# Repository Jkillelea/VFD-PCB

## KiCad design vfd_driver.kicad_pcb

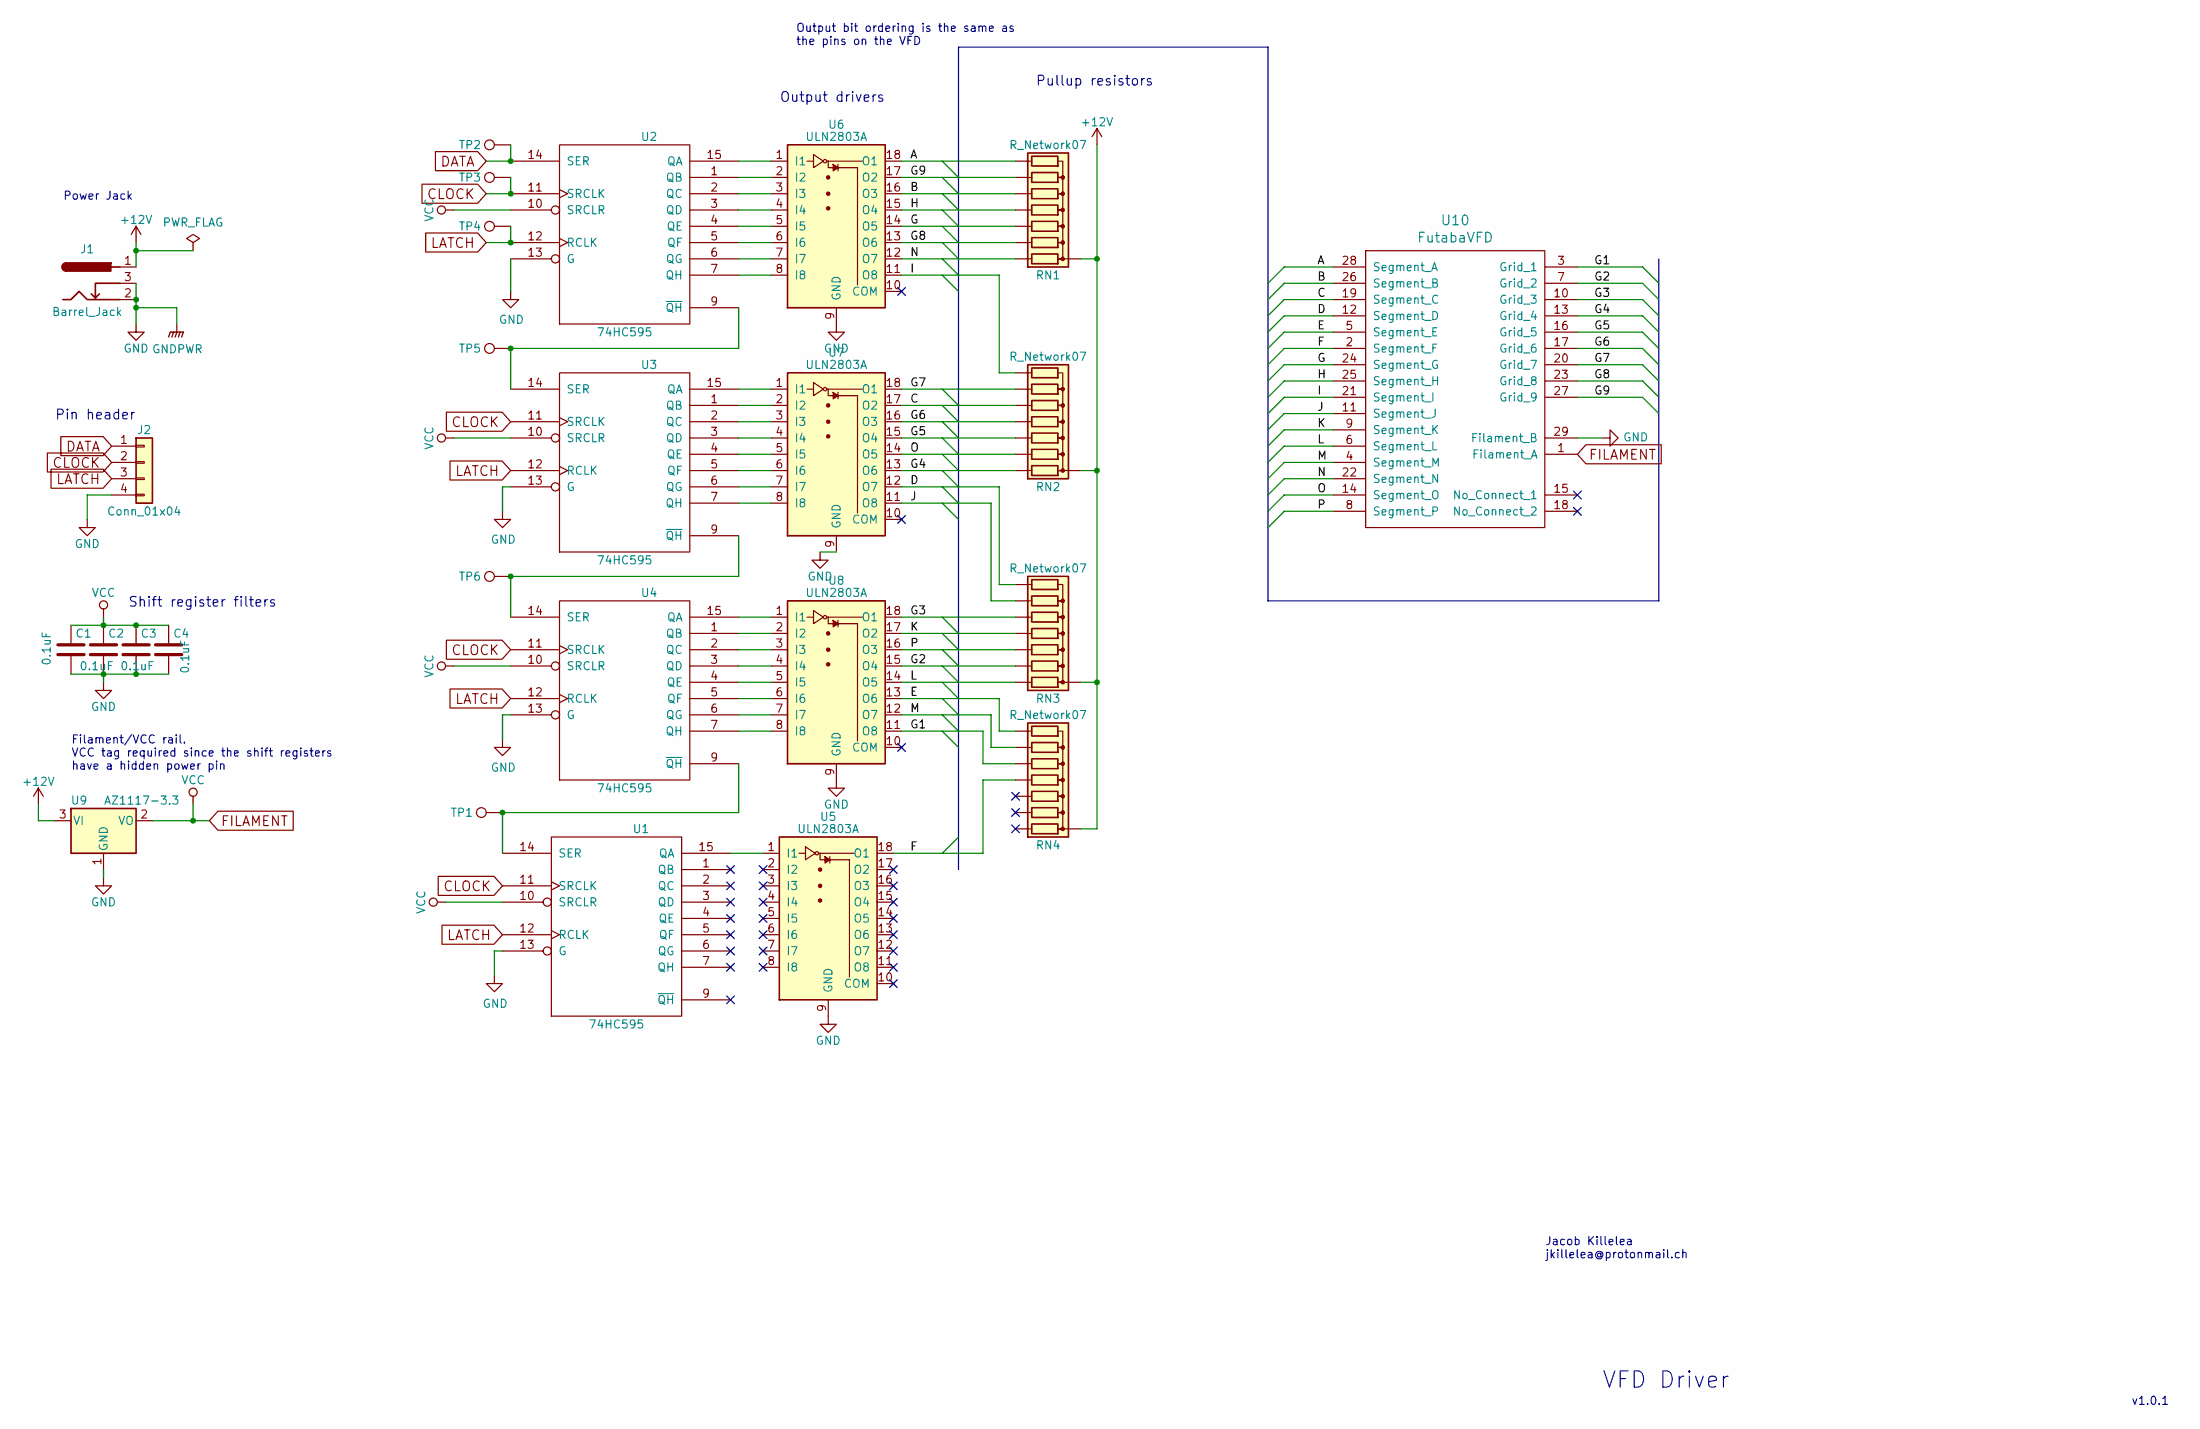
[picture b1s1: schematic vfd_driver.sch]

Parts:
C1, C2, C3, C4: 0.1uF; C_Disc_D4.3mm_W1.9mm_P5.00mm
J1: Barrel_Jack; BARREL_JACK
J2: Conn_01x04; Pin_Header_Angled_1x04_Pitch2.54mm
RN1, RN2, RN3, RN4: R_Network07; R_Array_SIP8
TP1, TP2, TP3, TP4, TP5, TP6: TestPoint; TestPoint_Pad_D1.0mm
U1, U2, U3, U4: 74HC595; DIP-16_W7.62mm_LongPads
U5, U6, U7, U8: ULN2803A; DIP-18_W7.62mm_LongPads
U9: AZ1117-3.3; TO-220-3_Horizontal_Reversed
U10: FutabaVFD; Futaba VFD

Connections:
+12V: J1.1, RN1.1 (common), RN2.1 (common), RN3.1 (common), RN4.1 (common), U9.3 (VI)
/A: RN1.8 (R7), U6.18 (O1), U10.28 (Segment_A)
/B: RN1.6 (R5), U6.16 (O3), U10.26 (Segment_B)
/C: RN2.6 (R5), U7.17 (O2), U10.19 (Segment_C)
/D: RN3.8 (R7), U7.12 (O7), U10.12 (Segment_D)
/E: RN4.8 (R7), U8.13 (O6), U10.5 (Segment_E)
/F: RN4.5 (R4), U5.18 (O1), U10.2 (Segment_F)
/G: RN1.4 (R3), U6.14 (O5), U10.24 (Segment_G)
/G1: RN4.6 (R5), U8.11 (O8), U10.3 (Grid_1)
/G2: RN3.3 (R2), U8.15 (O4), U10.7 (Grid_2)
/G3: RN3.6 (R5), U8.18 (O1), U10.10 (Grid_3)
/G4: RN2.2 (R1), U7.13 (O6), U10.13 (Grid_4)
/G5: RN2.4 (R3), U7.15 (O4), U10.16 (Grid_5)
/G6: RN2.5 (R4), U7.16 (O3), U10.17 (Grid_6)
/G7: RN2.7 (R6), U7.18 (O1), U10.20 (Grid_7)
/G8: RN1.3 (R2), U6.13 (O6), U10.23 (Grid_8)
/G9: RN1.7 (R6), U6.17 (O2), U10.27 (Grid_9)
/H: RN1.5 (R4), U6.15 (O4), U10.25 (Segment_H)
/I: RN2.8 (R7), U6.11 (O8), U10.21 (Segment_I)
/J: RN3.7 (R6), U7.11 (O8), U10.11 (Segment_J)
/K: RN3.5 (R4), U8.17 (O2), U10.9 (Segment_K)
/L: RN3.2 (R1), U8.14 (O5), U10.6 (Segment_L)
/M: RN4.7 (R6), U8.12 (O7), U10.4 (Segment_M)
/N: RN1.2 (R1), U6.12 (O7), U10.22 (Segment_N)
/O: RN2.3 (R2), U7.14 (O5), U10.14 (Segment_O)
/P: RN3.4 (R3), U8.16 (O3), U10.8 (Segment_P)
CLOCK: J2.2, TP3.1, U1.11 (SRCLK), U2.11 (SRCLK), U3.11 (SRCLK), U4.11 (SRCLK)
DATA: J2.1, TP2.1, U2.14 (SER)
FILAMENT: C1.1, C2.1, C3.1, C4.1, U1.10 (SRCLR), U1.16 (VCC), U2.10 (SRCLR), U2.16 (VCC), U3.10 (SRCLR), U3.16 (VCC), U4.10 (SRCLR), U4.16 (VCC), U9.2 (VO), U10.1 (Filament_A)
GND: C1.2, C2.2, C3.2, C4.2, J1.2, J1.3, J2.4, U1.8 (GND), U1.13 (G), U2.8 (GND), U2.13 (G), U3.8 (GND), U3.13 (G), U4.8 (GND), U4.13 (G), U5.9 (GND), U6.9 (GND), U7.9 (GND), U8.9 (GND), U9.1 (GND), U10.29 (Filament_B)
LATCH: J2.3, TP4.1, U1.12 (RCLK), U2.12 (RCLK), U3.12 (RCLK), U4.12 (RCLK)
unnamed: TP1.1, U1.14 (SER), U4.9 (~QH)
unnamed: TP5.1, U2.9 (~QH), U3.14 (SER)
unnamed: TP6.1, U3.9 (~QH), U4.14 (SER)
unnamed: U1.15 (QA), U5.1 (I1)
unnamed: U2.1 (QB), U6.2 (I2)
unnamed: U2.2 (QC), U6.3 (I3)
unnamed: U2.3 (QD), U6.4 (I4)
unnamed: U2.4 (QE), U6.5 (I5)
unnamed: U2.5 (QF), U6.6 (I6)
unnamed: U2.6 (QG), U6.7 (I7)
unnamed: U2.7 (QH), U6.8 (I8)
unnamed: U2.15 (QA), U6.1 (I1)
unnamed: U3.1 (QB), U7.2 (I2)
unnamed: U3.2 (QC), U7.3 (I3)
unnamed: U3.3 (QD), U7.4 (I4)
unnamed: U3.4 (QE), U7.5 (I5)
unnamed: U3.5 (QF), U7.6 (I6)
unnamed: U3.6 (QG), U7.7 (I7)
unnamed: U3.7 (QH), U7.8 (I8)
unnamed: U3.15 (QA), U7.1 (I1)
unnamed: U4.1 (QB), U8.2 (I2)
unnamed: U4.2 (QC), U8.3 (I3)
unnamed: U4.3 (QD), U8.4 (I4)
unnamed: U4.4 (QE), U8.5 (I5)
unnamed: U4.5 (QF), U8.6 (I6)
unnamed: U4.6 (QG), U8.7 (I7)
unnamed: U4.7 (QH), U8.8 (I8)
unnamed: U4.15 (QA), U8.1 (I1)

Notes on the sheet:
Pullup resistors
Output drivers
Shift register filters
Pin header
VFD Driver
v1.0.1
Jacob Killelea jkillelea@protonmail.ch
Power Jack
Filament/VCC rail. VCC tag required since the shift registers have a hidden power pin
Output bit ordering is the same as the pins on the VFD

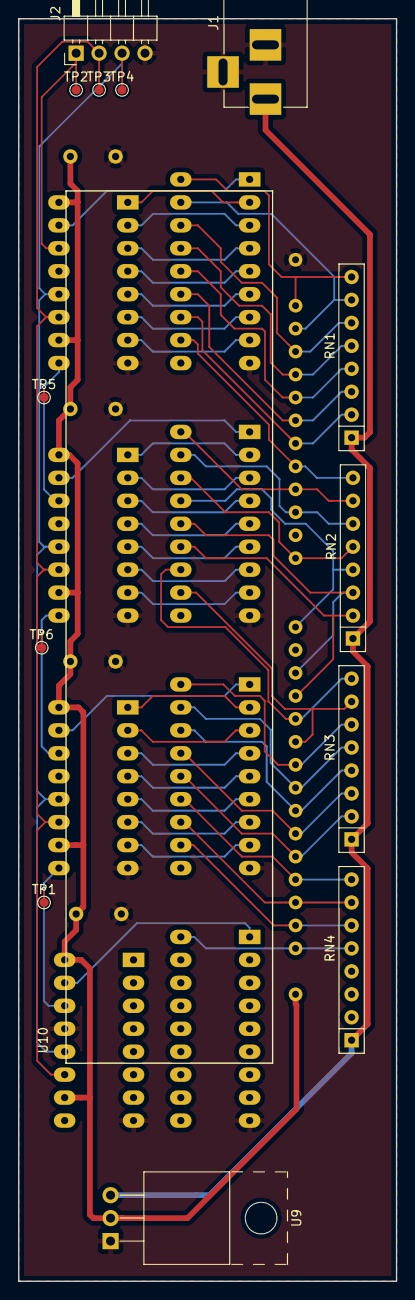
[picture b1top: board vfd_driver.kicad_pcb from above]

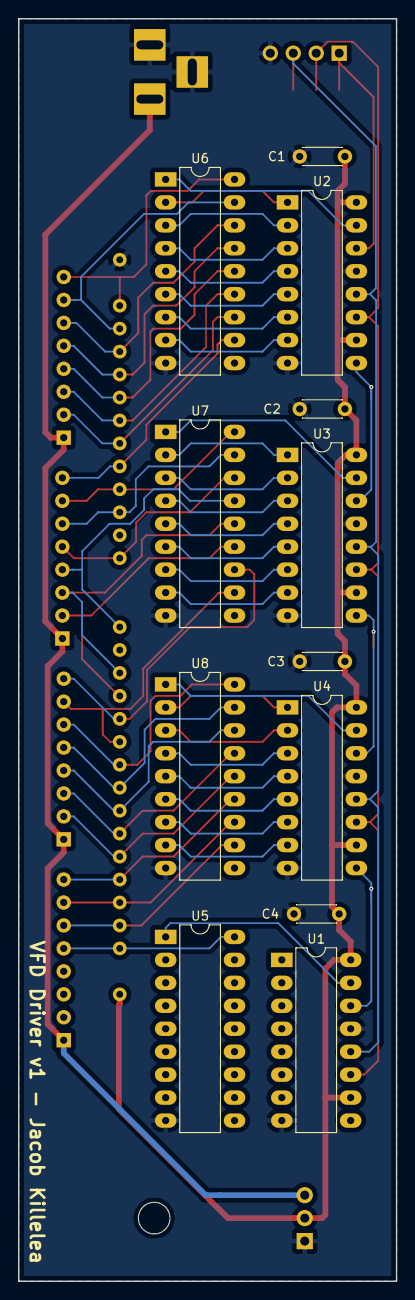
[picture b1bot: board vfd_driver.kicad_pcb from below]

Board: 2 copper layers, 41.8 x 139.7 mm, 26 parts (12 on the bottom side), 59 nets.

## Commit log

2019-11-09 Initial commit. First rev fabricated + headers
2020-04-12 submodule init, VFD arduino code
2020-04-12 submodule update
